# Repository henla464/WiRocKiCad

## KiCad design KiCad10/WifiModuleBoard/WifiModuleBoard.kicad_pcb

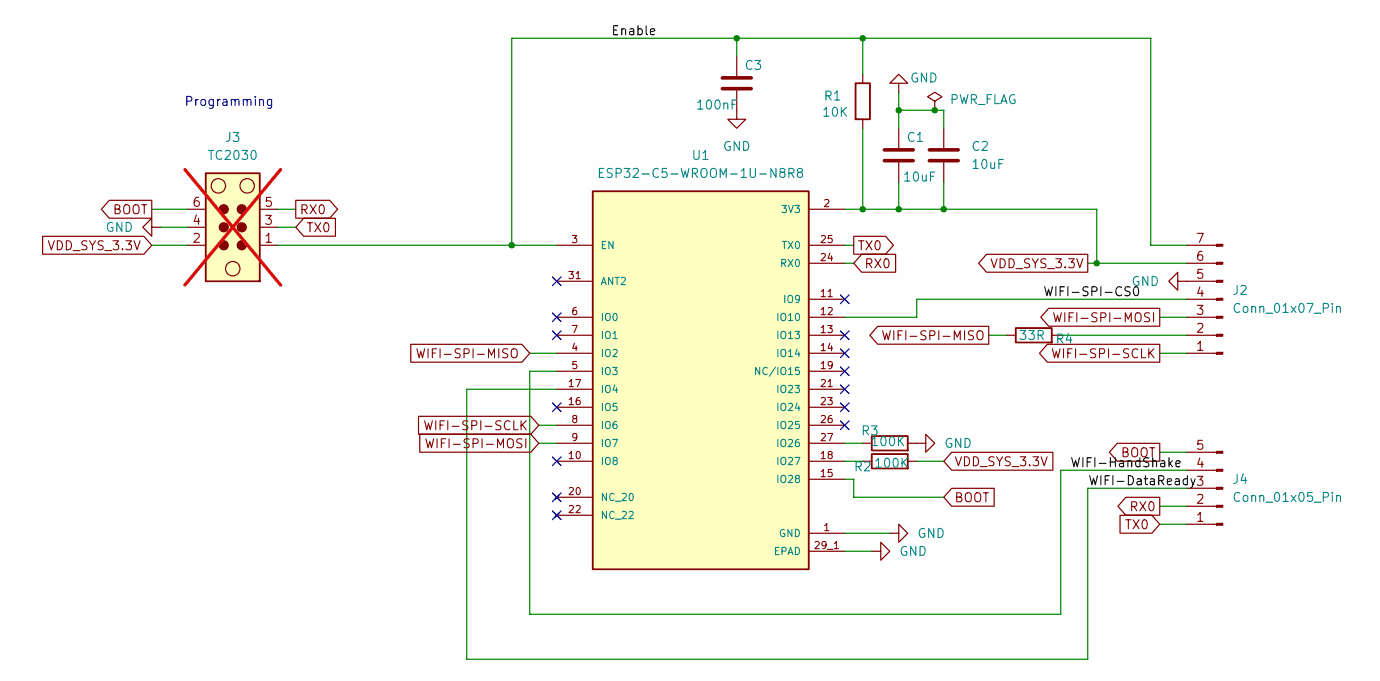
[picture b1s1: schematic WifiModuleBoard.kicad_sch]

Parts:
C1, C2: 10uF; C_0402_1005Metric_Pad0.74x0.62mm_HandSolder; ManufacturerPartNumber CL05A106MQ5NUNC; LCSC Part# C15525
C3: 100nF; C_0402_1005Metric_Pad0.74x0.62mm_HandSolder; ManufacturerPartNumber CL05B104KO5NNNC; LCSC Part# C1525
J2: Conn_01x07_Pin; PinSocket_1x07_P1.27mm_Vertical_SMD_Pin1Left
J3: TC2030; Tag-Connect_TC2030-IDC-NL_2x03_P1.27mm_Vertical; not fitted
J4: Conn_01x05_Pin; PinSocket_1x05_P1.27mm_Vertical_SMD_Pin1Left
R1: 10K; R_0402_1005Metric_Pad0.72x0.64mm_HandSolder; ManufacturerPartNumber 0402WGF1002TCE; LCSC Part# C25744
R2, R3: 100K; R_0402_1005Metric_Pad0.72x0.64mm_HandSolder; ManufacturerPartNumber 0402WGF1003TCE; LCSC Part# C25741
R4: 33R; R_0402_1005Metric_Pad0.72x0.64mm_HandSolder; ManufacturerPartNumber 0402WGF330JTCE; LCSC Part# C25105
U1: ESP32-C5-WROOM-1U-N8R8; XCVR_ESP32-C5-WROOM-1U-N8R8; PARTREV 0.7

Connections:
/Enable: C3.1, J2.7, J3.1, R1.1, U1.3 (EN)
/WIFI-DataReady: J4.3, U1.17 (IO4)
/WIFI-HandShake: J4.4, U1.5 (IO3)
/WIFI-SPI-CS0: J2.4, U1.12 (IO10)
BOOT: J3.6, J4.5, U1.15 (IO28)
GND: C1.1, C2.1, C3.2, J2.5, J3.4, R3.2, U1.1 (GND), U1.28 (GND), U1.29_1 (EPAD), U1.29_2 (EPAD), U1.29_3 (EPAD), U1.29_4 (EPAD), U1.29_5 (EPAD), U1.29_6 (EPAD), U1.29_7 (EPAD), U1.29_8 (EPAD), U1.29_9 (EPAD), U1.30 (GND), U1.32 (GND)
unnamed: J2.2, R4.2
unnamed: R3.1, U1.27 (IO26)
unnamed: R2.1, U1.18 (IO27)
RX0: J3.5, J4.2, U1.24 (RX0)
TX0: J3.3, J4.1, U1.25 (TX0)
VDD_SYS_3.3V: C1.2, C2.2, J2.6, J3.2, R1.2, R2.2, U1.2 (3V3)
WIFI-SPI-MISO: R4.1, U1.4 (IO2)
WIFI-SPI-MOSI: J2.3, U1.9 (IO7)
WIFI-SPI-SCLK: J2.1, U1.8 (IO6)

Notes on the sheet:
Programming

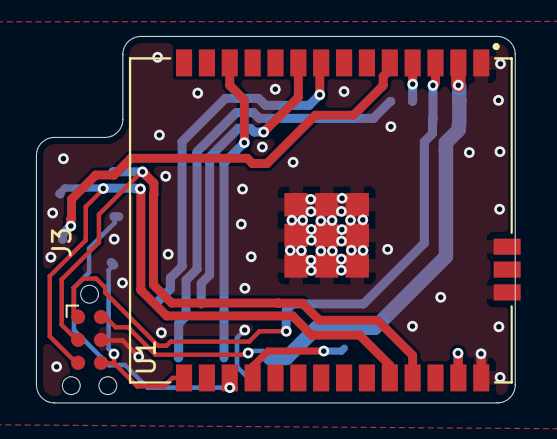
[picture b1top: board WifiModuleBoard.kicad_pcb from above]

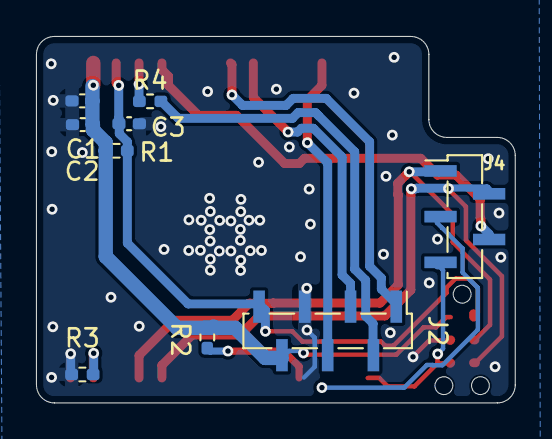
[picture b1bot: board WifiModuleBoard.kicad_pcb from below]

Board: 2 copper layers, 26.6 x 20.4 mm, 11 parts (9 on the bottom side), 15 nets.

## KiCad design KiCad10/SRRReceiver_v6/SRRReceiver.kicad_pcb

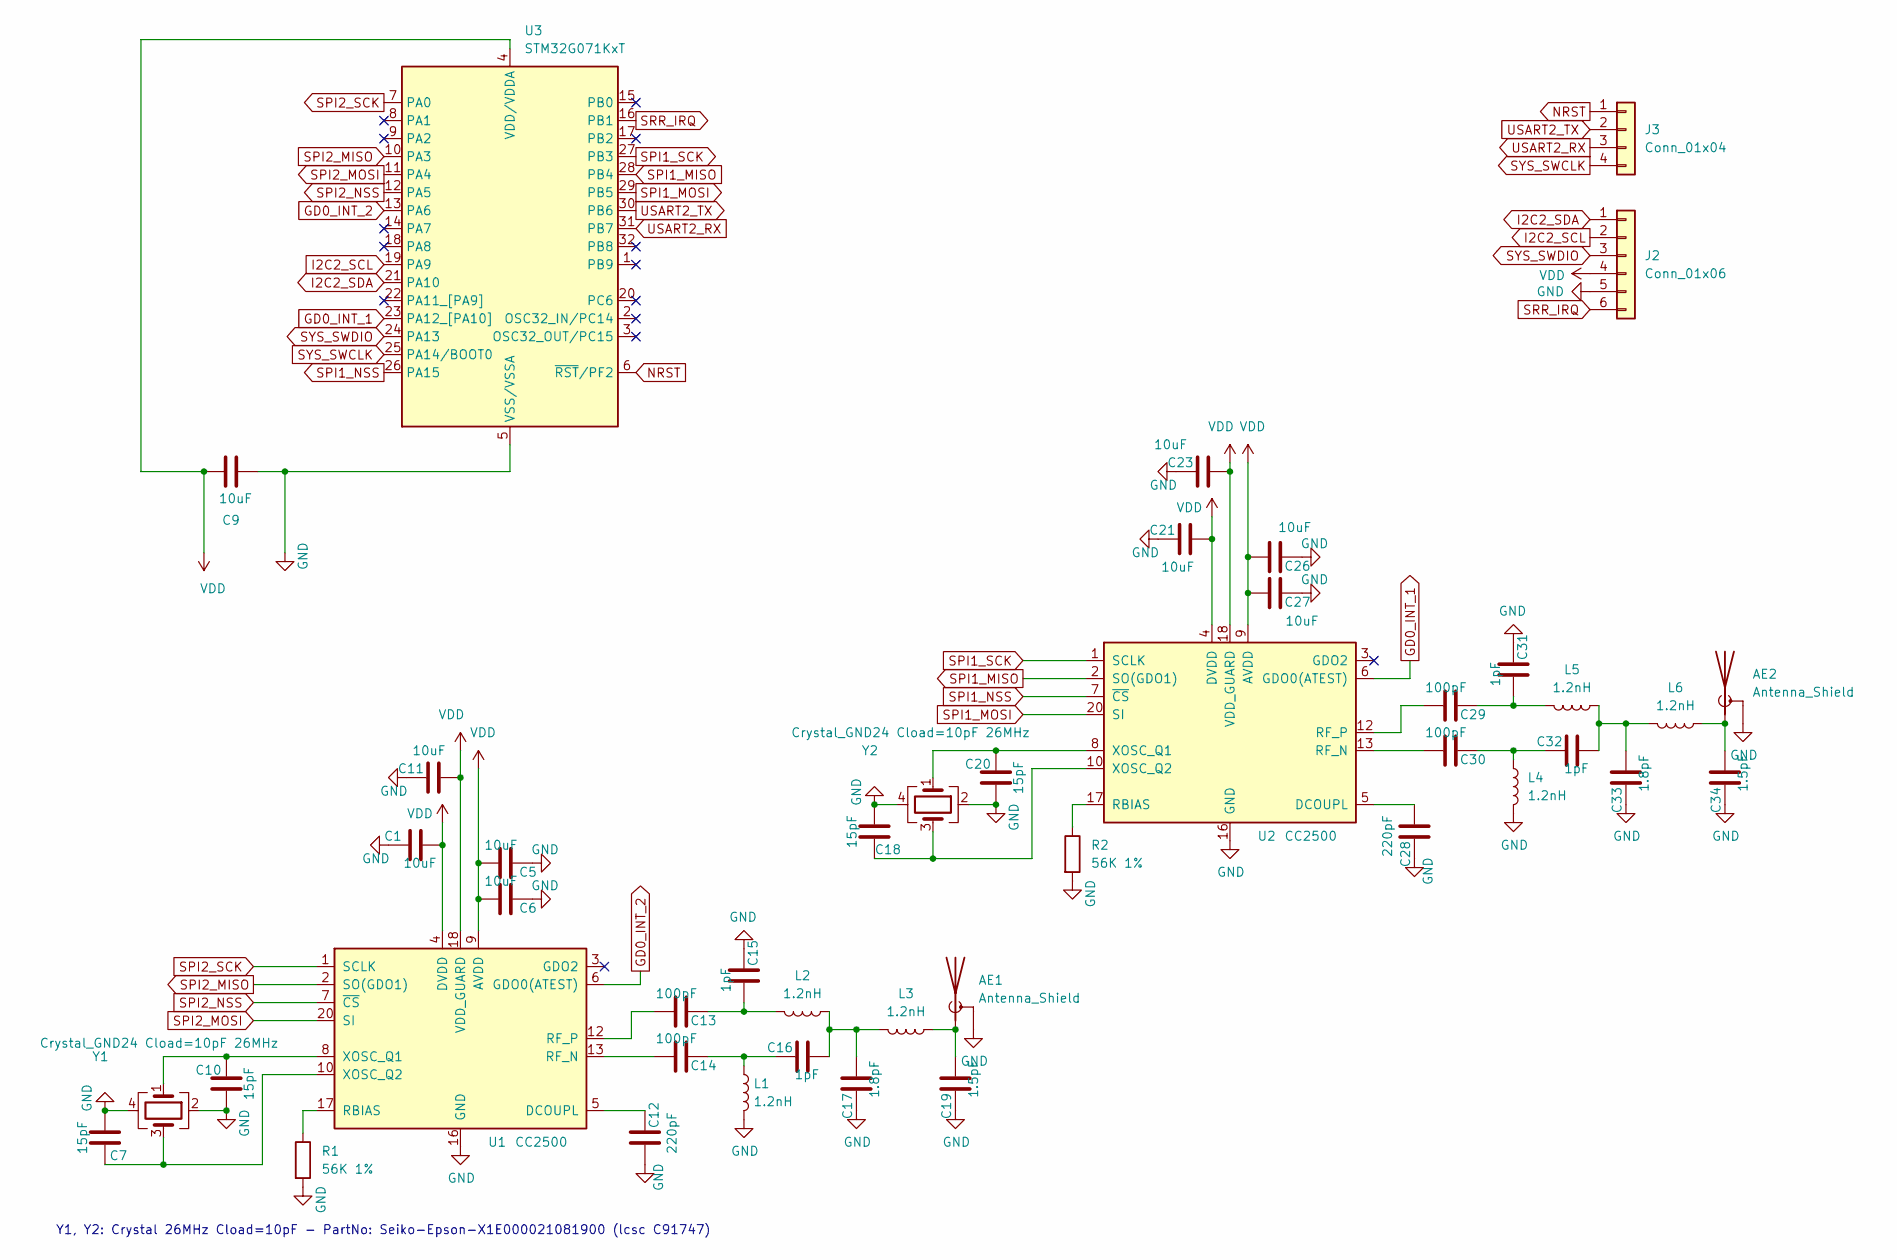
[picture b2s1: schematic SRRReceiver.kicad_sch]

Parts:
AE1, AE2: Antenna_Shield; Texas_SWRA117D_2.4GHz_Right-TunedForWiroc
C1, C5, C6, C11, C21, C23, C26, C27: 10uF; C_0402_1005Metric; LCSC C15525
C7, C10, C18, C20: 15pF; C_0402_1005Metric; LCSC C1548
C9: 10uF; C_0402_1005Metric_Pad0.74x0.62mm_HandSolder; LCSC C15525
C12, C28: 220pF; C_0402_1005Metric; LCSC C16772
C13, C14, C29, C30: 100pF; C_0402_1005Metric; LCSC C1546
C15, C16, C31, C32: 1pF; C_0402_1005Metric; LCSC C1550
C17, C33: 1.8pF; C_0402_1005Metric; LCSC C76902
C19, C34: 1.5pF; C_0402_1005Metric; LCSC C282238
J2: Conn_01x06; PinSocket_1x06_P1.27mm_Vertical
J3: Conn_01x04; PinSocket_1x04_P1.27mm_Vertical
L1, L2, L3, L4, L5, L6: 1.2nH; L_0402_1005Metric; LCSC C445745
R1, R2: 56K 1%; R_0402_1005Metric; LCSC C25796
U1, U2: CC2500; Texas_S-PVQFN-N20_EP2.4x2.4mm; LCSC C57494
U3: STM32G071KxT; LQFP-32_7x7mm_P0.8mm; LCSC C529339
Y1, Y2: Crystal_GND24 Cload=10pF 26MHz; Crystal_SMD_3225-4Pin_3.2x2.5mm; LCSC C91747

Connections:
GD0_INT_1: U2.6 (GDO0(ATEST)), U3.23 (PA12_[PA10])
GD0_INT_2: U1.6 (GDO0(ATEST)), U3.13 (PA6)
GND: AE1.2 (Shield), AE2.2 (Shield), C1.1, C5.1, C6.1, C7.1, C9.1, C10.1, C11.1, C12.2, C15.1, C17.1, C18.1, C19.1, C20.1, C21.1, C23.1, C26.1, C27.1, C28.1, C31.1, C33.1, C34.1, J2.5, L1.2, L4.2, R1.2, R2.2, U1.16 (GND), U1.19 (GND), U1.21 (GND), U2.16 (GND), U2.19 (GND), U2.21 (GND), U3.5 (VSS/VSSA), Y1.2, Y1.4, Y2.2, Y2.4
I2C2_SCL: J2.2, U3.19 (PA9)
I2C2_SDA: J2.1, U3.21 (PA10)
NRST: J3.1, U3.6 (~RST/PF2)
unnamed: AE1.1 (A), C19.2, L3.1
unnamed: AE2.1 (A), C34.2, L6.1
unnamed: C13.1, C15.2, L2.2
unnamed: C14.1, C16.1, L1.1
unnamed: C16.2, C17.2, L2.1, L3.2
unnamed: C29.1, C31.2, L5.2
unnamed: C30.1, C32.1, L4.1
unnamed: C32.2, C33.2, L5.1, L6.2
unnamed: C12.1, U1.5 (DCOUPL)
unnamed: R1.1, U1.17 (RBIAS)
unnamed: C14.2, U1.13 (RF_N)
unnamed: C13.2, U1.12 (RF_P)
unnamed: C10.2, U1.8 (XOSC_Q1), Y1.1
unnamed: C7.2, U1.10 (XOSC_Q2), Y1.3
unnamed: C28.2, U2.5 (DCOUPL)
unnamed: R2.1, U2.17 (RBIAS)
unnamed: C30.2, U2.13 (RF_N)
unnamed: C29.2, U2.12 (RF_P)
unnamed: C20.2, U2.8 (XOSC_Q1), Y2.1
unnamed: C18.2, U2.10 (XOSC_Q2), Y2.3
SPI1_MISO: U2.2 (SO(GDO1)), U3.28 (PB4)
SPI1_MOSI: U2.20 (SI), U3.29 (PB5)
SPI1_NSS: U2.7 (~CS), U3.26 (PA15)
SPI1_SCK: U2.1 (SCLK), U3.27 (PB3)
SPI2_MISO: U1.2 (SO(GDO1)), U3.10 (PA3)
SPI2_MOSI: U1.20 (SI), U3.11 (PA4)
SPI2_NSS: U1.7 (~CS), U3.12 (PA5)
SPI2_SCK: U1.1 (SCLK), U3.7 (PA0)
SRR_IRQ: J2.6, U3.16 (PB1)
SYS_SWCLK: J3.4, U3.25 (PA14/BOOT0)
SYS_SWDIO: J2.3, U3.24 (PA13)
USART2_RX: J3.3, U3.31 (PB7)
USART2_TX: J3.2, U3.30 (PB6)
VDD: C1.2, C5.2, C6.2, C9.2, C11.2, C21.2, C23.2, C26.2, C27.2, J2.4, U1.4 (DVDD), U1.9 (AVDD), U1.11 (AVDD), U1.14 (AVDD), U1.15 (AVDD), U1.18 (VDD_GUARD), U2.4 (DVDD), U2.9 (AVDD), U2.11 (AVDD), U2.14 (AVDD), U2.15 (AVDD), U2.18 (VDD_GUARD), U3.4 (VDD/VDDA)

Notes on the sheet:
Y1, Y2: Crystal 26MHz Cload=10pF - PartNo: Seiko-Epson-X1E000021081900 (lcsc C91747)

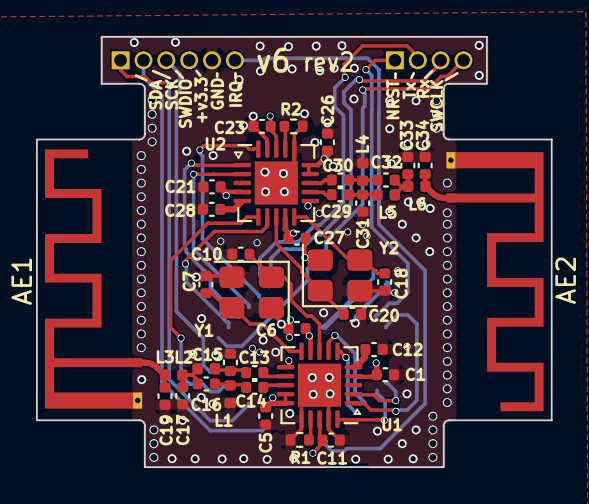
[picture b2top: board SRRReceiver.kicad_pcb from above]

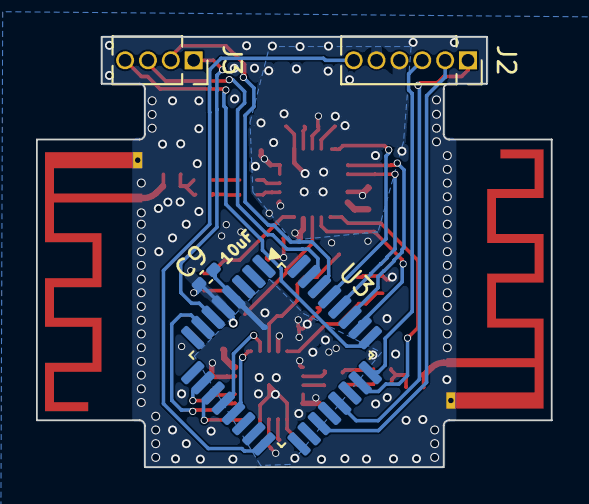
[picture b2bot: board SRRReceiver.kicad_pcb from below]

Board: 4 copper layers, 28.6 x 23.9 mm, 44 parts (4 on the bottom side), 40 nets.

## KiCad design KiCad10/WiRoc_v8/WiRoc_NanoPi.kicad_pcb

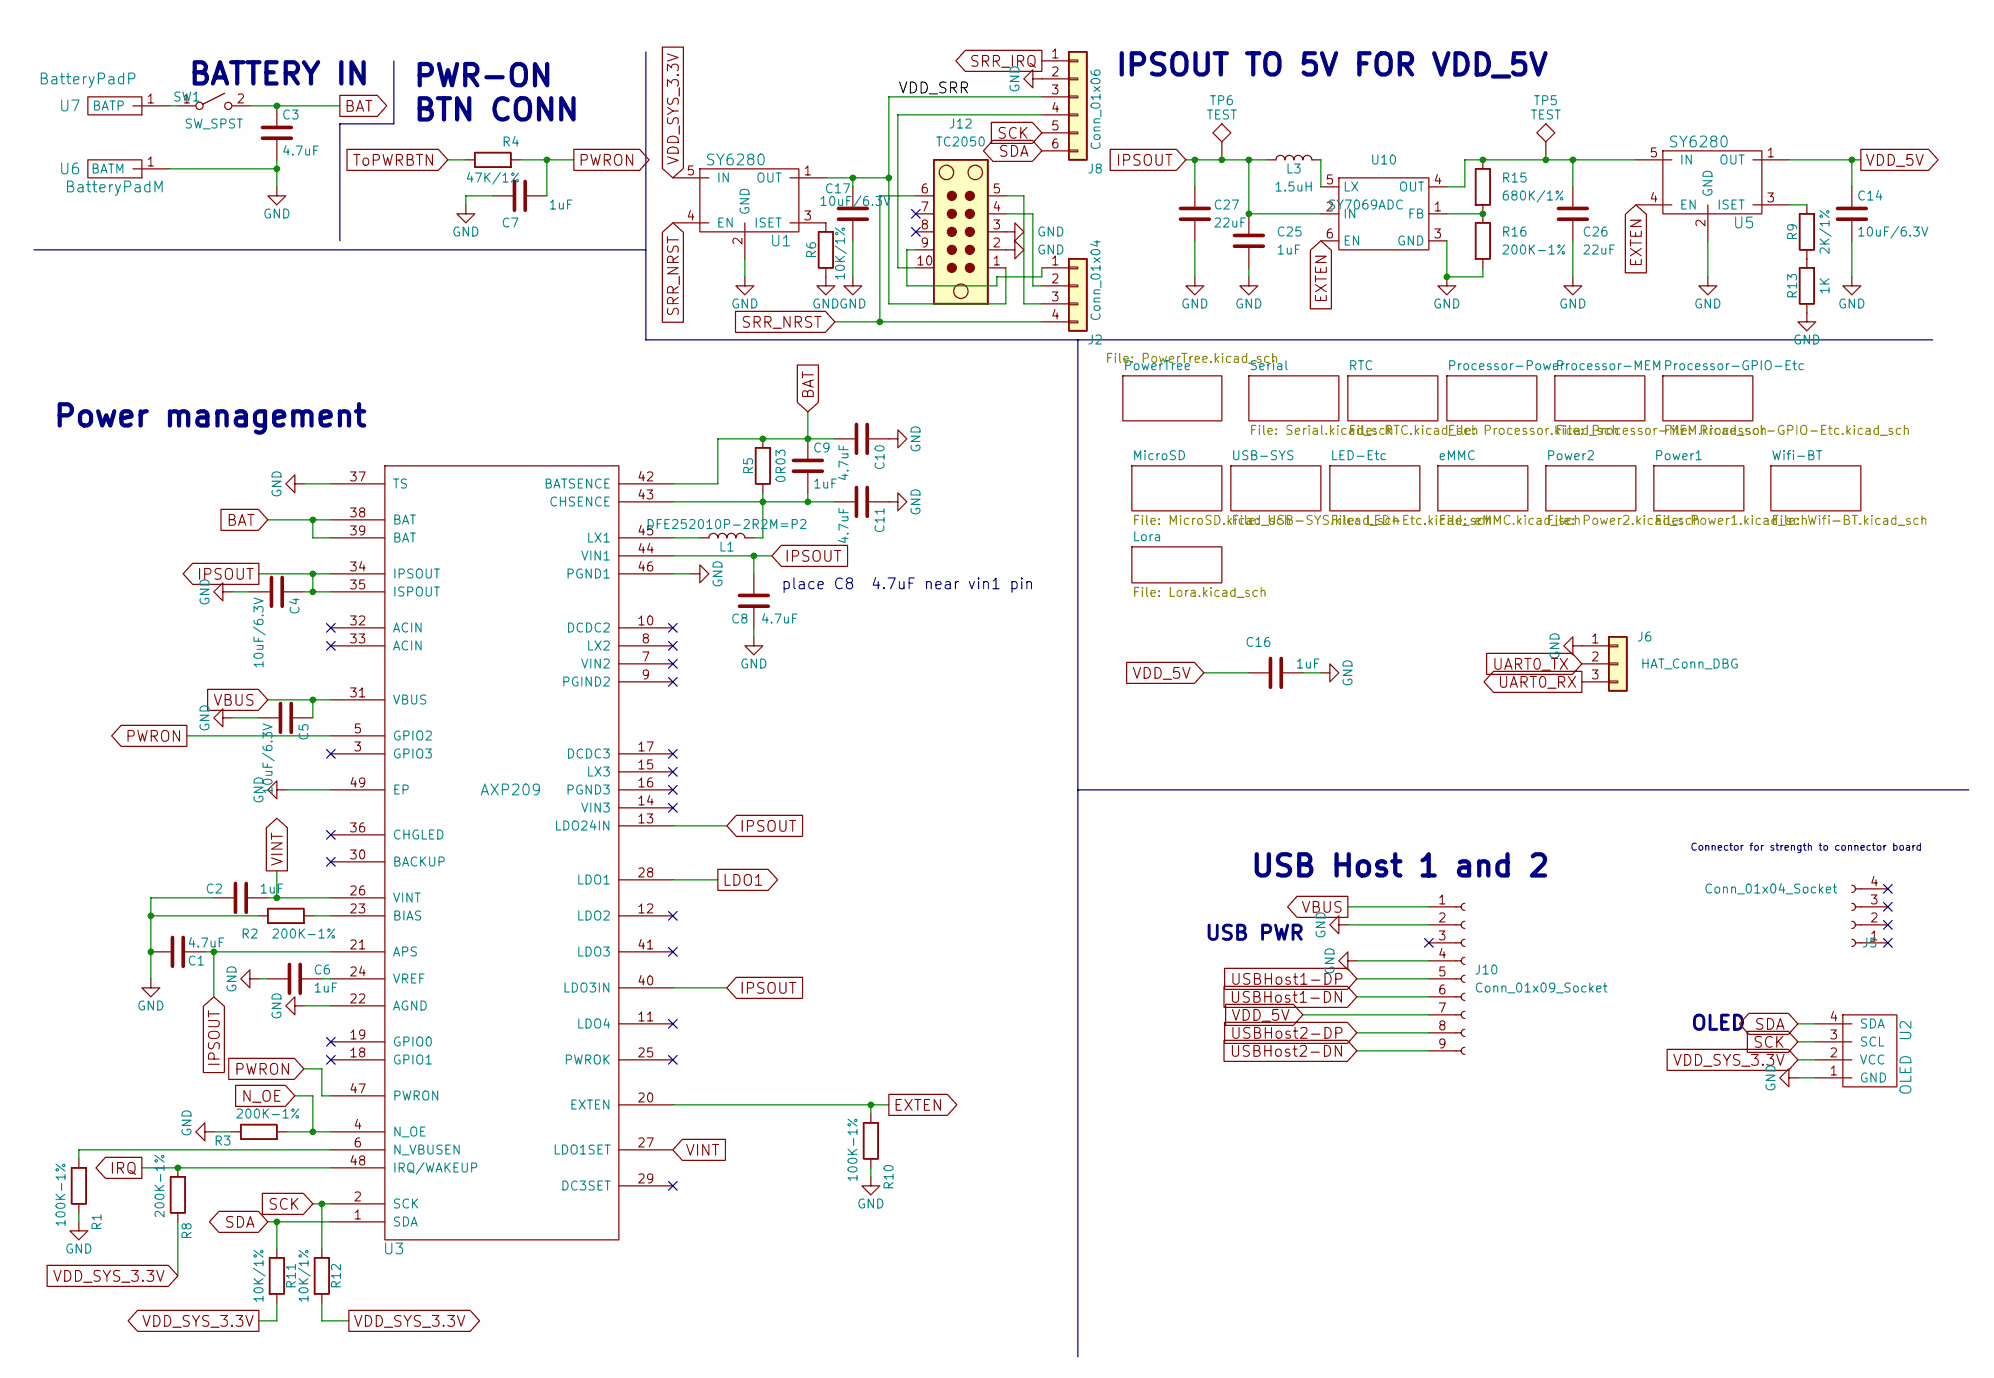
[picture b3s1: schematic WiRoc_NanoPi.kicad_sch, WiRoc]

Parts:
C1, C3, C8, C10, C11: 4.7uF; C_0402_1005Metric; ManufacturerPartNumber CL05A475MP5NRNC; LCSC Part # C23733
C2, C6, C7, C9, C16, C25: 1uF; C_0402_1005Metric; ManufacturerPartNumber CL05A105KA5NQNC; LCSC Part # C52923
C4, C5, C14, C17: 10uF/6.3V; C_0402_1005Metric; ManufacturerPartNumber CL05A106MQ5NUNC; LCSC Part # C15525
C26, C27: 22uF; C_0603_1608Metric; ManufacturerPartNumber GRM188R61A226ME15D; LCSC Part # C84419
J2: Conn_01x04; PinSocket_1x04_P1.27mm_RightAngled
J5: Conn_01x04_Socket; PinSocket_1x04_P1.27mm_Vertical; ManufacturerPartNumber PM127V-11-04-H46; JLCBasicExtended Extended
J6: HAT_Conn_DBG; Pin_Header_Straight_1x03_Pitch2.54mm; ManufacturerPartNumber 2.54mm 1x40P
J8: Conn_01x06; PinSocket_1x06_P1.27mm_RightAngled
J10: Conn_01x09_Socket; PinSocket_1x09_P1.27mm_Vertical; ManufacturerPartNumber PM127V-11-09-H46; JLCBasicExtended Extended
J12: TC2050; Tag-Connect_TC2050-IDC-NL_2x05_P1.27mm_Vertical
L1: DFE252010P-2R2M=P2; L_1008_2520Metric; ManufacturerPartNumber DFE252012F‑2R2M=P2; LCSC Part # C576403
L3: 1.5uH; L_1008_2520Metric; ManufacturerPartNumber DFE252012F-1R5M=P2; LCSC Part # C909806
R1, R10: 100K-1%; R_0402_1005Metric; ManufacturerPartNumber 0402WGF1003TCE; LCSC Part # C25741
R2, R3, R8, R16: 200K-1%; R_0402_1005Metric; ManufacturerPartNumber 0402WGF2003TCE; LCSC Part # C25764
R4: 47K/1%; R_0402_1005Metric; ManufacturerPartNumber 0402WGF4702TCE; LCSC Part # C25792
R5: 0R03; R_0805_2012Metric; ManufacturerPartNumber 0805W4F300MT5E; LCSC Part # C247605
R6, R11, R12: 10K/1%; R_0402_1005Metric; ManufacturerPartNumber 0402WGF1002TCE; LCSC Part # C25744
R9: 2K/1%; R_0402_1005Metric; ManufacturerPartNumber 0402WGF2001TCE; LCSC Part # C4109
R13: 1K; R_0402_1005Metric; ManufacturerPartNumber 0402WGF1001TCE; LCSC Part # C11702
R15: 680K/1%; R_0402_1005Metric; ManufacturerPartNumber 0402WGF6803TCE; LCSC Part # C4131
SW1: SW_SPST; Pin_Header_Straight_1x02_Pitch2.54mm; ManufacturerPartNumber 2.54mm 1x40P
TP5, TP6: TEST; TestPoint_Pad_D1.0mm
U1, U5: SY6280; SOT-23-5; ManufacturerPartNumber SY6280AAC; LCSC Part # C55136
U2: OLED; CONN_OLED_TWI-Socket_Strip_Straight_1x04_Pitch2.54mm; ManufacturerPartNumber 2.54mm 1x40P
U3: AXP209; qfn48_6x6mm_Pitch0.4mm; ManufacturerPartNumber AXP209; LCSC Part # C2997895
U6: BatteryPadM; BatteryPad
U7: BatteryPadP; BatteryPadThinner
U10: SY7069ADC; TSOT-23-6; PartNo SY7069ADC; LCSC Part # C207630

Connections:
/VDD_SRR: C17.1, J8.3, J12.1, U1.1 (OUT)
BAT: C3.1, C9.1, C10.2, R5.2, SW1.2 (B), U3.38 (BAT), U3.39 (BAT), U3.42 (BATSENCE)
EXTEN: R10.2, U3.20 (EXTEN), U5.4 (EN), U10.6 (EN); also elsewhere on the board
GND: C1.2, C2.2, C3.2, C4.2, C5.2, C6.2, C7.1, C8.1, C10.1, C11.1, C14.2, C16.2, C17.2, C25.2, C26.2, C27.2, J6.1, J8.2, J10.2, J10.4, J12.2, J12.3, R1.1, R2.1, R3.1, R6.1, R10.1, R13.1, R16.2, U1.2 (GND), U2.1 (GND), U3.22 (AGND), U3.37 (TS), U3.46 (PGND1), U3.49 (EP), U5.2 (GND), U6.1 (BATM_1), U10.3 (GND); also elsewhere on the board
IPSOUT: C1.1, C4.1, C8.2, C25.1, C27.1, L3.1, TP6.1, U3.13 (LDO24IN), U3.21 (APS), U3.34 (IPSOUT), U3.35 (ISPOUT), U3.40 (LDO3IN), U3.44 (VIN1), U10.2 (IN); also elsewhere on the board
IRQ: R8.2, U3.48 (IRQ/WAKEUP); also elsewhere on the board
LDO1: U3.28 (LDO1); also elsewhere on the board
N_OE: R3.2, U3.4 (N_OE); also elsewhere on the board
unnamed: J2.1, J12.9
unnamed: J2.2, J12.4
unnamed: J2.3, J12.5
unnamed: J8.4, J12.10
unnamed: R9.1, R13.2
unnamed: SW1.1 (A), U7.1 (BATP_1)
unnamed: R6.2, U1.3 (ISET)
unnamed: R2.2, U3.23 (BIAS)
unnamed: C9.2, C11.2, L1.2, R5.1, U3.43 (CHSENCE)
unnamed: L1.1, U3.45 (LX1)
unnamed: R1.2, U3.6 (N_VBUSEN)
unnamed: C6.1, U3.24 (VREF)
unnamed: R9.2, U5.3 (ISET)
unnamed: R15.2, R16.1, U10.1 (FB)
unnamed: L3.2, U10.5 (LX)
unnamed: C26.1, R15.1, TP5.1, U5.5 (IN), U10.4 (OUT)
PWRON: C7.2, R4.2, U3.5 (GPIO2), U3.47 (PWRON)
SCK: J8.5, R12.1, U2.3 (SCL), U3.2 (SCK); also elsewhere on the board
SDA: J8.6, R11.1, U2.4 (SDA), U3.1 (SDA); also elsewhere on the board
SRR_IRQ: J8.1; also elsewhere on the board
SRR_NRST: J2.4, J12.6, U1.4 (EN); also elsewhere on the board
ToPWRBTN: R4.1; also elsewhere on the board
UART0_RX: J6.3; also elsewhere on the board
UART0_TX: J6.2; also elsewhere on the board
USBHost1-DN: J10.6; also elsewhere on the board
USBHost1-DP: J10.5; also elsewhere on the board
USBHost2-DN: J10.9; also elsewhere on the board
USBHost2-DP: J10.8; also elsewhere on the board
VBUS: C5.1, J10.1, U3.31 (VBUS)
VDD_5V: C14.1, C16.1, J10.7, U5.1 (OUT); also elsewhere on the board
VDD_SYS_3.3V: R8.1, R11.2, R12.2, U1.5 (IN), U2.2 (VCC); also elsewhere on the board
VINT: C2.1, U3.26 (VINT), U3.27 (LDO1SET)

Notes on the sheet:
place C8 4.7uF near vin1 pin
USB PWR
IPSOUT TO 5V FOR VDD_5V
PWR-ON BTN CONN
Power management
OLED
Connector for strength to connector board
USB Host 1 and 2
BATTERY IN

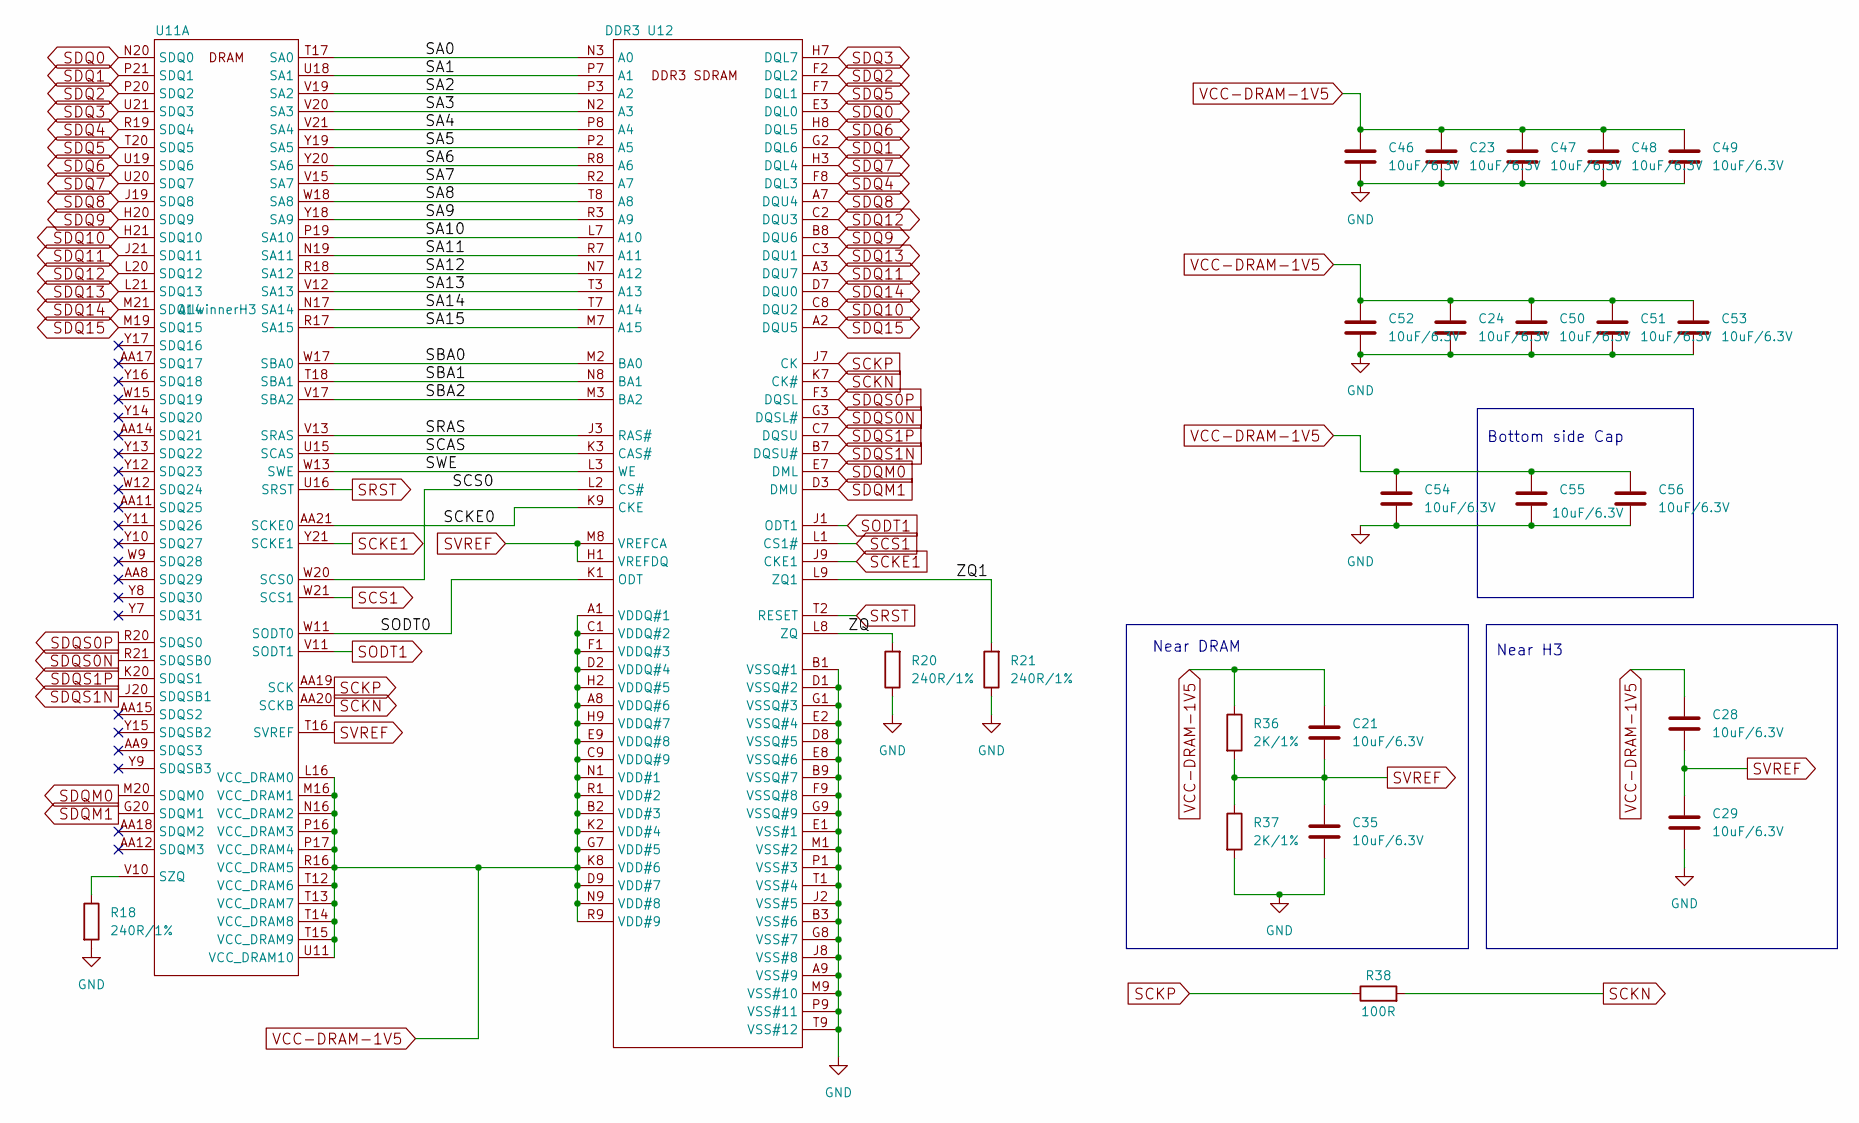
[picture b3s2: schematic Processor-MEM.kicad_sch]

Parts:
C21, C23, C24, C28, C29, C35, C46, C47, C48, C49, C50, C51, C52, C53, C54, C55, C56: 10uF/6.3V; C_0402_1005Metric; ManufacturerPartNumber CL05A106MQ5NUNC; LCSC Part # C15525
R18, R20, R21: 240R/1%; R_0402_1005Metric; ManufacturerPartNumber RC0402FR-07240RL; JLCBasicExtended Extended
R36, R37: 2K/1%; R_0402_1005Metric; ManufacturerPartNumber 0402WGF2001TCE; JLCBasicExtended Basic
R38: 100R; R_0402_1005Metric; ManufacturerPartNumber RC0402FR-07100RL; JLCBasicExtended Basic
U11: AllwinnerH3; BGA-347_21x21_14.0x14.0mm; ManufacturerPartNumber H3; JLCBasicExtended Extended
U12: DDR3; FBGA-96_7.5x13mm_Layout9x16_P0.8mm; ManufacturerPartNumber H5TQ4G63EFR-RDC; JLCBasicExtended Extended

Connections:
/Processor-MEM/SA0: U11.T17 (SA0), U12.N3 (A0)
/Processor-MEM/SA1: U11.U18 (SA1), U12.P7 (A1)
/Processor-MEM/SA2: U11.V19 (SA2), U12.P3 (A2)
/Processor-MEM/SA3: U11.V20 (SA3), U12.N2 (A3)
/Processor-MEM/SA4: U11.V21 (SA4), U12.P8 (A4)
/Processor-MEM/SA5: U11.Y19 (SA5), U12.P2 (A5)
/Processor-MEM/SA6: U11.Y20 (SA6), U12.R8 (A6)
/Processor-MEM/SA7: U11.V15 (SA7), U12.R2 (A7)
/Processor-MEM/SA8: U11.W18 (SA8), U12.T8 (A8)
/Processor-MEM/SA9: U11.Y18 (SA9), U12.R3 (A9)
/Processor-MEM/SA10: U11.P19 (SA10), U12.L7 (A10)
/Processor-MEM/SA11: U11.N19 (SA11), U12.R7 (A11)
/Processor-MEM/SA12: U11.R18 (SA12), U12.N7 (A12)
/Processor-MEM/SA13: U11.V12 (SA13), U12.T3 (A13)
/Processor-MEM/SA14: U11.N17 (SA14), U12.T7 (A14)
/Processor-MEM/SA15: U11.R17 (SA15), U12.M7 (A15)
/Processor-MEM/SBA0: U11.W17 (SBA0), U12.M2 (BA0)
/Processor-MEM/SBA1: U11.T18 (SBA1), U12.N8 (BA1)
/Processor-MEM/SBA2: U11.V17 (SBA2), U12.M3 (BA2)
/Processor-MEM/SCAS: U11.U15 (SCAS), U12.K3 (CAS#)
/Processor-MEM/SCKE0: U11.AA21 (SCKE0), U12.K9 (CKE)
/Processor-MEM/SCS0: U11.W20 (SCS0), U12.L2 (CS#)
/Processor-MEM/SODT0: U11.W11 (SODT0), U12.K1 (ODT)
/Processor-MEM/SRAS: U11.V13 (SRAS), U12.J3 (RAS#)
/Processor-MEM/SWE: U11.W13 (SWE), U12.L3 (WE)
/Processor-MEM/ZQ: R20.2, U12.L8 (ZQ)
/Processor-MEM/ZQ1: R21.2, U12.L9 (ZQ1)
GND: C23.2, C24.2, C29.2, C35.2, C46.2, C47.2, C48.2, C49.2, C50.2, C51.2, C52.2, C53.2, C54.2, C55.2, C56.2, R18.2, R20.1, R21.1, R37.2, U12.A9 (VSS#9), U12.B1 (VSSQ#1), U12.B3 (VSS#6), U12.B9 (VSSQ#7), U12.D1 (VSSQ#2), U12.D8 (VSSQ#5), U12.E1 (VSS#1), U12.E2 (VSSQ#4), U12.E8 (VSSQ#6), U12.F9 (VSSQ#8), U12.G1 (VSSQ#3), U12.G8 (VSS#7), U12.G9 (VSSQ#9), U12.J2 (VSS#5), U12.J8 (VSS#8), U12.M1 (VSS#2), U12.M9 (VSS#10), U12.P1 (VSS#3), U12.P9 (VSS#11), U12.T1 (VSS#4), U12.T9 (VSS#12); also elsewhere on the board
unnamed: R18.1, U11.V10 (SZQ)
SCKE1: U11.Y21 (SCKE1), U12.J9 (CKE1)
SCKN: R38.2, U11.AA20 (SCKB), U12.K7 (CK#)
SCKP: R38.1, U11.AA19 (SCK), U12.J7 (CK)
SCS1: U11.W21 (SCS1), U12.L1 (CS1#)
SDQ0: U11.N20 (SDQ0), U12.E3 (DQL0)
SDQ1: U11.P21 (SDQ1), U12.G2 (DQL6)
SDQ2: U11.P20 (SDQ2), U12.F2 (DQL2)
SDQ3: U11.U21 (SDQ3), U12.H7 (DQL7)
SDQ4: U11.R19 (SDQ4), U12.F8 (DQL3)
SDQ5: U11.T20 (SDQ5), U12.F7 (DQL1)
SDQ6: U11.U19 (SDQ6), U12.H8 (DQL5)
SDQ7: U11.U20 (SDQ7), U12.H3 (DQL4)
SDQ8: U11.J19 (SDQ8), U12.A7 (DQU4)
SDQ9: U11.H20 (SDQ9), U12.B8 (DQU6)
SDQ10: U11.H21 (SDQ10), U12.C8 (DQU2)
SDQ11: U11.J21 (SDQ11), U12.A3 (DQU7)
SDQ12: U11.L20 (SDQ12), U12.C2 (DQU3)
SDQ13: U11.L21 (SDQ13), U12.C3 (DQU1)
SDQ14: U11.M21 (SDQ14), U12.D7 (DQU0)
SDQ15: U11.M19 (SDQ15), U12.A2 (DQU5)
SDQM0: U11.M20 (SDQM0), U12.E7 (DML)
SDQM1: U11.G20 (SDQM1), U12.D3 (DMU)
SDQS0N: U11.R21 (SDQSB0), U12.G3 (DQSL#)
SDQS0P: U11.R20 (SDQS0), U12.F3 (DQSL)
SDQS1N: U11.J20 (SDQSB1), U12.B7 (DQSU#)
SDQS1P: U11.K20 (SDQS1), U12.C7 (DQSU)
SODT1: U11.V11 (SODT1), U12.J1 (ODT1)
SRST: U11.U16 (SRST), U12.T2 (RESET)
SVREF: C21.2, C28.2, C29.1, C35.1, R36.2, R37.1, U11.T16 (SVREF), U12.H1 (VREFDQ), U12.M8 (VREFCA)
VCC-DRAM-1V5: C21.1, C23.1, C24.1, C28.1, C46.1, C47.1, C48.1, C49.1, C50.1, C51.1, C52.1, C53.1, C54.1, C55.1, C56.1, R36.1, U11.L16 (VCC_DRAM0), U11.M16 (VCC_DRAM1), U11.N16 (VCC_DRAM2), U11.P16 (VCC_DRAM3), U11.P17 (VCC_DRAM4), U11.R16 (VCC_DRAM5), U11.T12 (VCC_DRAM6), U11.T13 (VCC_DRAM7), U11.T14 (VCC_DRAM8), U11.T15 (VCC_DRAM9), U11.U11 (VCC_DRAM10), U12.A1 (VDDQ#1), U12.A8 (VDDQ#6), U12.B2 (VDD#3), U12.C1 (VDDQ#2), U12.C9 (VDDQ#9), U12.D2 (VDDQ#4), U12.D9 (VDD#7), U12.E9 (VDDQ#8), U12.F1 (VDDQ#3), U12.G7 (VDD#5), U12.H2 (VDDQ#5), U12.H9 (VDDQ#7), U12.K2 (VDD#4), U12.K8 (VDD#6), U12.N1 (VDD#1), U12.N9 (VDD#8), U12.R1 (VDD#2), U12.R9 (VDD#9); also elsewhere on the board

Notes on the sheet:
Near H3
Near DRAM
Bottom side Cap

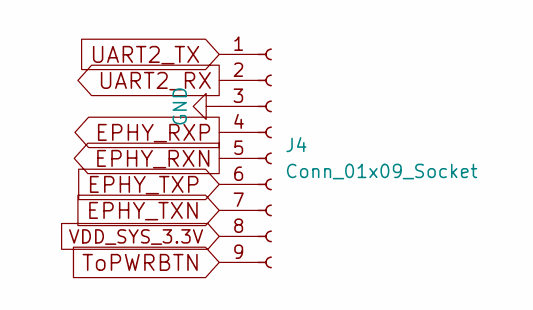
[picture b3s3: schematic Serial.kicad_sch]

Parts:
J4: Conn_01x09_Socket; PinSocket_1x09_P1.27mm_Vertical; ManufacturerPartNumber PM127V-11-09-H46; JLCBasicExtended Extended

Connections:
EPHY_RXN: J4.5; also elsewhere on the board
EPHY_RXP: J4.4; also elsewhere on the board
EPHY_TXN: J4.7; also elsewhere on the board
EPHY_TXP: J4.6; also elsewhere on the board
GND: J4.3; also elsewhere on the board
ToPWRBTN: J4.9; also elsewhere on the board
UART2_RX: J4.2; also elsewhere on the board
UART2_TX: J4.1; also elsewhere on the board
VDD_SYS_3.3V: J4.8; also elsewhere on the board

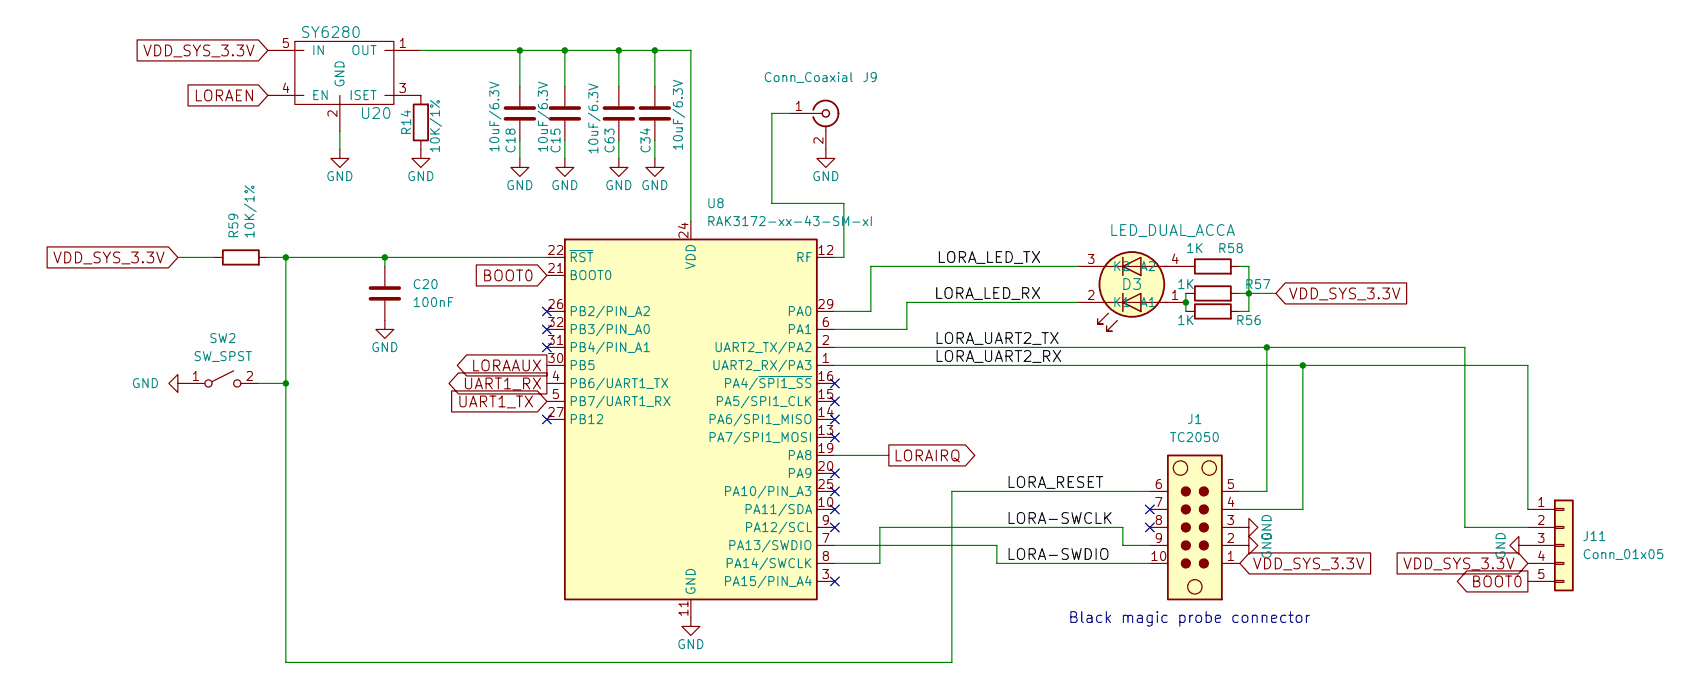
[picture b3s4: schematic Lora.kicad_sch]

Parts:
C15, C18, C34, C63: 10uF/6.3V; C_0402_1005Metric; ManufacturerPartNumber CL05A106MQ5NUNC; LCSC Part # C15525
C20: 100nF; C_0402_1005Metric; ManufacturerPartNumber CL05B104KO5NNNC; LCSC Part # C1525
D3: LED_DUAL_ACCA; LED_Dual_1.7_1.6; ManufacturerPartNumber HL-PCB-1617S9FH203BC; LCSC Part # C513363
J1: TC2050; Tag-Connect_TC2050-IDC-NL_2x05_P1.27mm_Vertical
J9: Conn_Coaxial; SMA_Amphenol_901-143_Horizontal
J11: Conn_01x05; PinHeader_1x05_P2.54mm_Vertical; ManufacturerPartNumber HB-PH3-25415PB2GOP; JLCBasicExtended Extended
R14: 10K/1%; R_0402_1005Metric; ManufacturerPartNumber 0402WGF1002TCE; LCSC Part # C25744
R56, R57, R58: 1K; R_0402_1005Metric; ManufacturerPartNumber 0402WGF1001TCE; LCSC Part # C11702
R59: 10K/1%; R_0402_1005Metric; ManufacturerPartNumber 0402WGF1002TCE; JLCBasicExtended Basic
SW2: SW_SPST; PinHeader_1x02_P1.27mm_Vertical
U8: RAK3172-xx-43-SM-xI; RAK3172
U20: SY6280; SOT-23-5; ManufacturerPartNumber SY6280AAC; LCSC Part # C55136

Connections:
/Lora/LORA-SWCLK: J1.9, U8.8 (PA14/SWCLK)
/Lora/LORA-SWDIO: J1.10, U8.7 (PA13/SWDIO)
/Lora/LORA_LED_RX: D3.2 (K1), U8.6 (PA1)
/Lora/LORA_LED_TX: D3.3 (K2), U8.29 (PA0)
/Lora/LORA_RESET: C20.1, J1.6, R59.2, SW2.2 (B), U8.22 (~RST)
/Lora/LORA_UART2_RX: J1.4, J11.1, U8.1 (UART2_RX/PA3)
/Lora/LORA_UART2_TX: J1.5, J11.2, U8.2 (UART2_TX/PA2)
BOOT0: J11.5, U8.21 (BOOT0)
GND: C15.2, C18.2, C20.2, C34.2, C63.2, J1.2, J1.3, J9.2 (Ext), J11.3, R14.1, SW2.1 (A), U8.11 (GND), U8.17 (GND), U8.18 (GND), U8.23 (GND), U8.28 (GND), U20.2 (GND); also elsewhere on the board
LORAAUX: U8.30 (PB5); also elsewhere on the board
LORAEN: U20.4 (EN); also elsewhere on the board
LORAIRQ: U8.19 (PA8); also elsewhere on the board
unnamed: D3.1 (A1), R56.1, R57.1
unnamed: D3.4 (A2), R58.1
unnamed: J9.1 (In), U8.12 (RF)
unnamed: R14.2, U20.3 (ISET)
unnamed: C15.1, C18.1, C34.1, C63.1, U8.24 (VDD), U20.1 (OUT)
UART1_RX: U8.4 (PB6/UART1_TX); also elsewhere on the board
UART1_TX: U8.5 (PB7/UART1_RX); also elsewhere on the board
VDD_SYS_3.3V: J1.1, J11.4, R56.2, R57.2, R58.2, R59.1, U20.5 (IN); also elsewhere on the board

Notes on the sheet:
Black magic probe connector

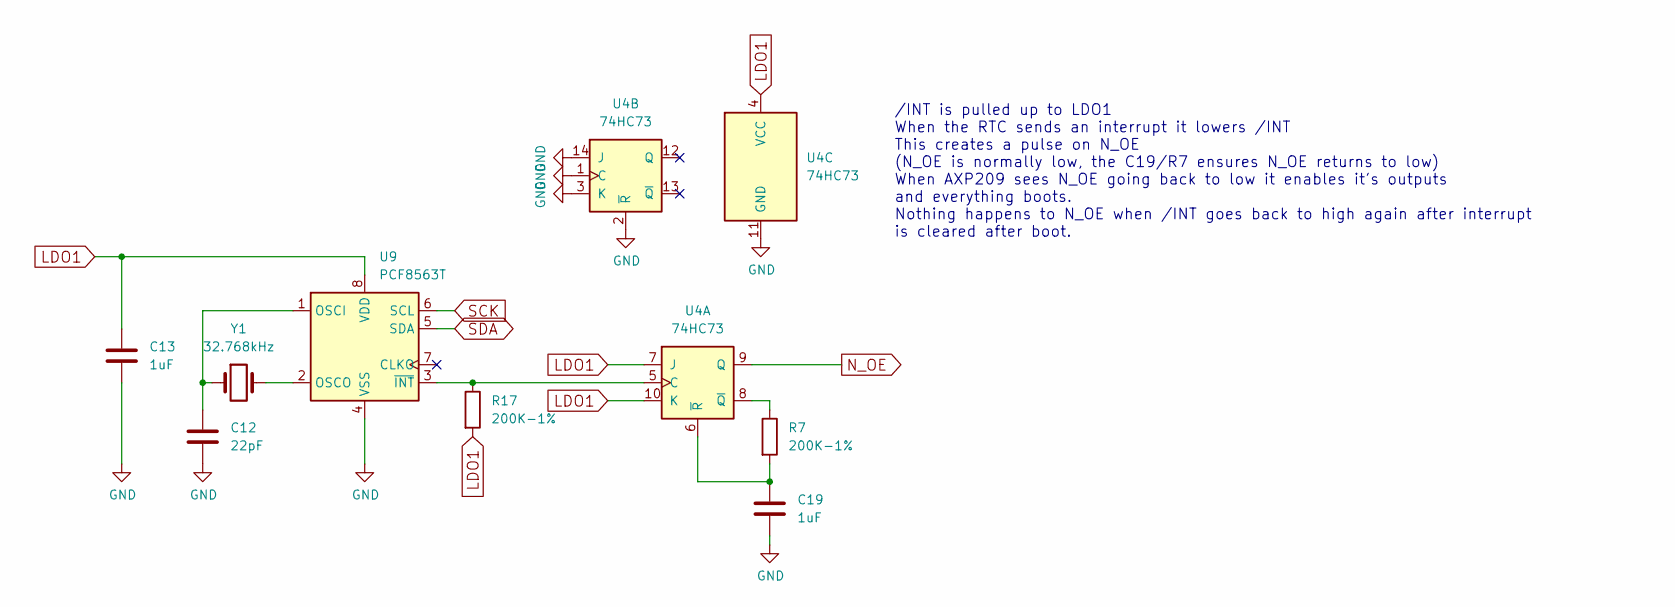
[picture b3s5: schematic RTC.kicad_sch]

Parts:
C12: 22pF; C_0402_1005Metric; ManufacturerPartNumber 0402CG220J500NT; LCSC Part # C1555
C13, C19: 1uF; C_0402_1005Metric; ManufacturerPartNumber CL05A105KA5NQNC; LCSC Part # C52923
R7, R17: 200K-1%; R_0402_1005Metric; ManufacturerPartNumber 0402WGF2003TCE; LCSC Part # C25764
U4: 74HC73; SOIC-14_3.9x8.7mm_P1.27mm; ManufacturerPartNumber CD74HC73M96; LCSC Part # C350539
U9: PCF8563T; SOIC-8_3.9x4.9mm_P1.27mm; ManufacturerPartNumber PCF8563T/5,518; LCSC Part # C7440
Y1: 32.768kHz; SMD3215-2P; ManufacturerPartNumber Q13FC1350000400; LCSC Part # C32346

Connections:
GND: C12.2, C13.2, C19.2, U4.1 (C), U4.2 (~R), U4.3 (K), U4.11 (GND), U4.14 (J), U9.4 (VSS); also elsewhere on the board
LDO1: C13.1, R17.2, U4.4 (VCC), U4.7 (J), U4.10 (K), U9.8 (VDD); also elsewhere on the board
N_OE: U4.9 (Q); also elsewhere on the board
unnamed: R17.1, U4.5 (C), U9.3 (~INT)
unnamed: R7.1, U4.8 (~Q)
unnamed: C19.1, R7.2, U4.6 (~R)
unnamed: C12.1, U9.1 (OSCI), Y1.1
unnamed: U9.2 (OSCO), Y1.2
SCK: U9.6 (SCL); also elsewhere on the board
SDA: U9.5 (SDA); also elsewhere on the board

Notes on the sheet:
/INT is pulled up to LDO1 When the RTC sends an interrupt it lowers /INT This creates a pulse on N_OE (N_OE is normally low, the C19/R7 ensures N_OE returns to low) When AXP209 sees N_OE going back to low it enables it's outputs and everything boots. Nothing happens to N_OE when /INT goes back to h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
